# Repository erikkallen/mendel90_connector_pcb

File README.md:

# Mendel90 connector PCB

If you happen to own a mendel90 and want a different way to connect your hotend and accesories, you could use this.

Support the following hotend goodies:

* BL touch
* Nema17 Stepper
* End stop (Same as bl touch wires)
* LED Strip
* Hotend fan
* Part cool fan (12v/5v)
* Hotend heater
* Thermocouple breakout board(Max6675/Max31855)

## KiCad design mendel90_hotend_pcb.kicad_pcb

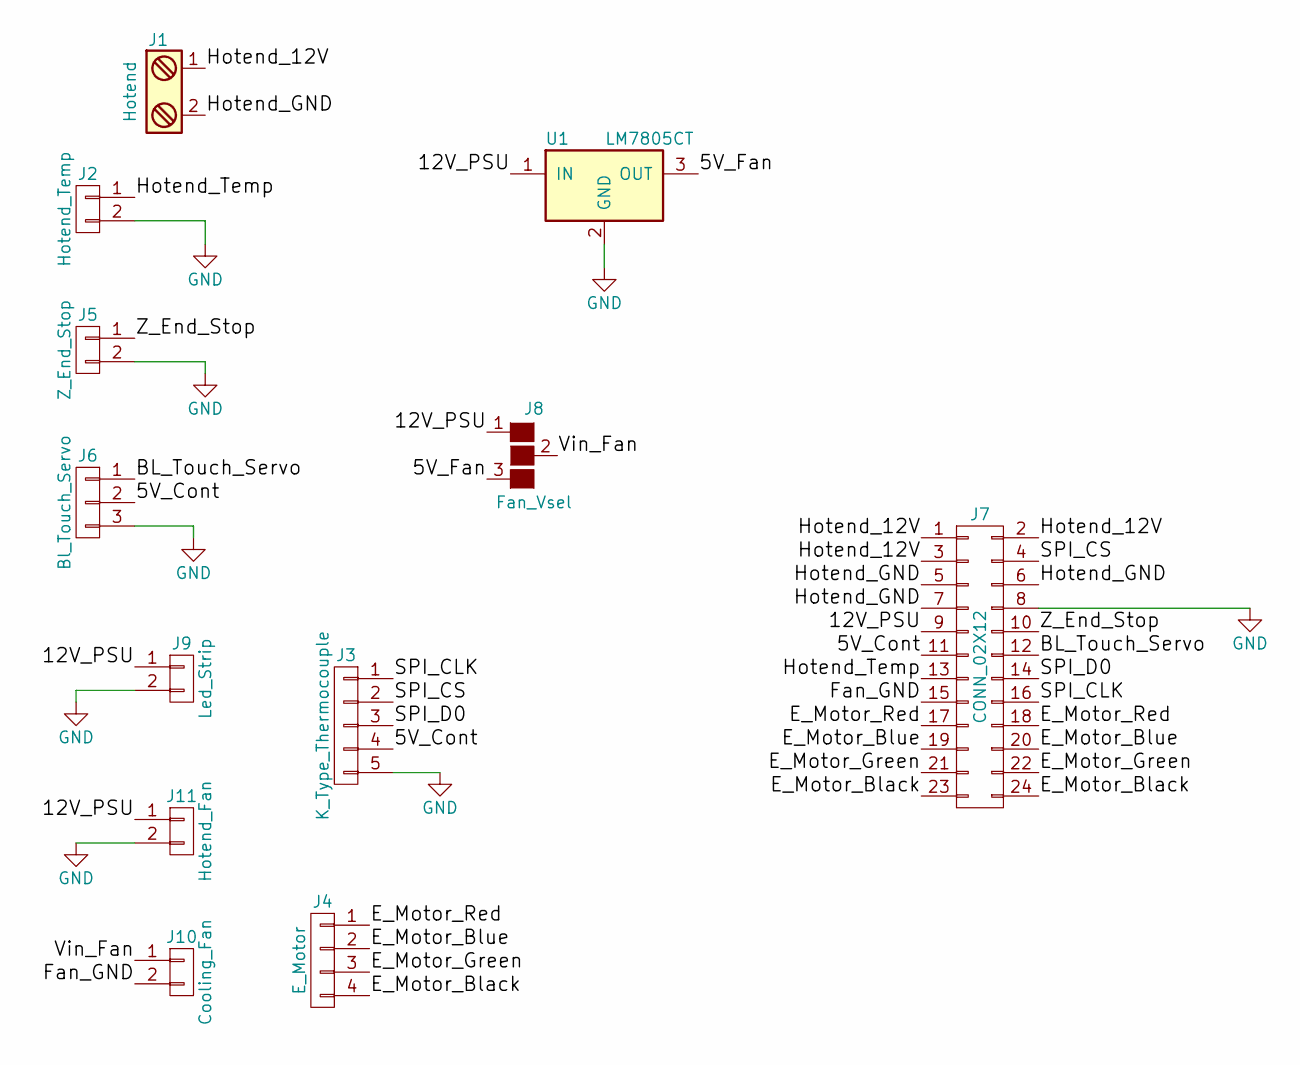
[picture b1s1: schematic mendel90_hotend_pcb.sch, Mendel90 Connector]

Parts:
J1: Hotend; TerminalBlock_Pheonix_MKDS1.5-2pol
J2: Hotend_Temp; Pin_Header_Straight_1x02_Pitch2.54mm
J3: K_Type_Thermocouple; Pin_Header_Straight_1x05_Pitch2.54mm
J4: E_Motor; Pin_Header_Straight_1x04_Pitch2.54mm
J5: Z_End_Stop; Pin_Header_Straight_1x02_Pitch2.54mm
J6: Bl_Touch_Servo; Pin_Header_Straight_1x03_Pitch2.54mm
J7: CONN_02X12; Pin_Header_Angled_2x12_Pitch2.54mm
J8: Fan_Vsel; GS3
J9: Led_Strip; Pin_Header_Straight_1x02_Pitch2.54mm
J10: Cooling_Fan; Pin_Header_Straight_1x02_Pitch2.54mm
J11: Hotend_Fan; Pin_Header_Straight_1x02_Pitch2.54mm
U1: LM7805CT; TO-220_Vertical

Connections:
/5V_Cont: J3.4, J6.2, J7.11
/5V_Fan: J8.3 (G3), U1.3 (OUT)
/12V_PSU: J7.9, J8.1 (G1), J9.1, J11.1, U1.1 (IN)
/BL_Touch_Servo: J6.1, J7.12
/E_Motor_Black: J4.4, J7.23, J7.24
/E_Motor_Blue: J4.2, J7.19, J7.20
/E_Motor_Green: J4.3, J7.21, J7.22
/E_Motor_Red: J4.1, J7.17, J7.18
/Fan_GND: J7.15, J10.2
/Hotend_12V: J1.1, J7.1, J7.2, J7.3
/Hotend_GND: J1.2, J7.5, J7.6, J7.7
/Hotend_Temp: J2.1, J7.13
/SPI_CLK: J3.1, J7.16
/SPI_CS: J3.2, J7.4
/SPI_D0: J3.3, J7.14
/Vin_Fan: J8.2 (G2), J10.1
/Z_End_Stop: J5.1, J7.10
GND: J2.2, J3.5, J5.2, J6.3, J7.8, J9.2, J11.2, U1.2 (GND)

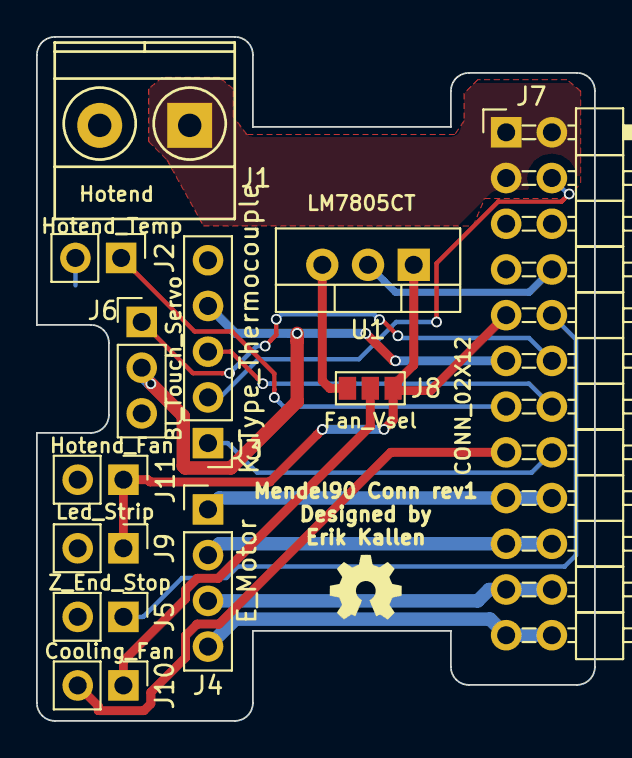
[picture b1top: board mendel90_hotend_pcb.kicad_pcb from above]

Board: 2 copper layers, 31.0 x 38.0 mm, 12 parts (0 on the bottom side), 18 nets.

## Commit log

2017-07-07 added schematic and readme
